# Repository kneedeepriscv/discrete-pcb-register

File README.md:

# discrete-pcb-register
PCB for the register for the KneeDeep RISCV Discrete Build

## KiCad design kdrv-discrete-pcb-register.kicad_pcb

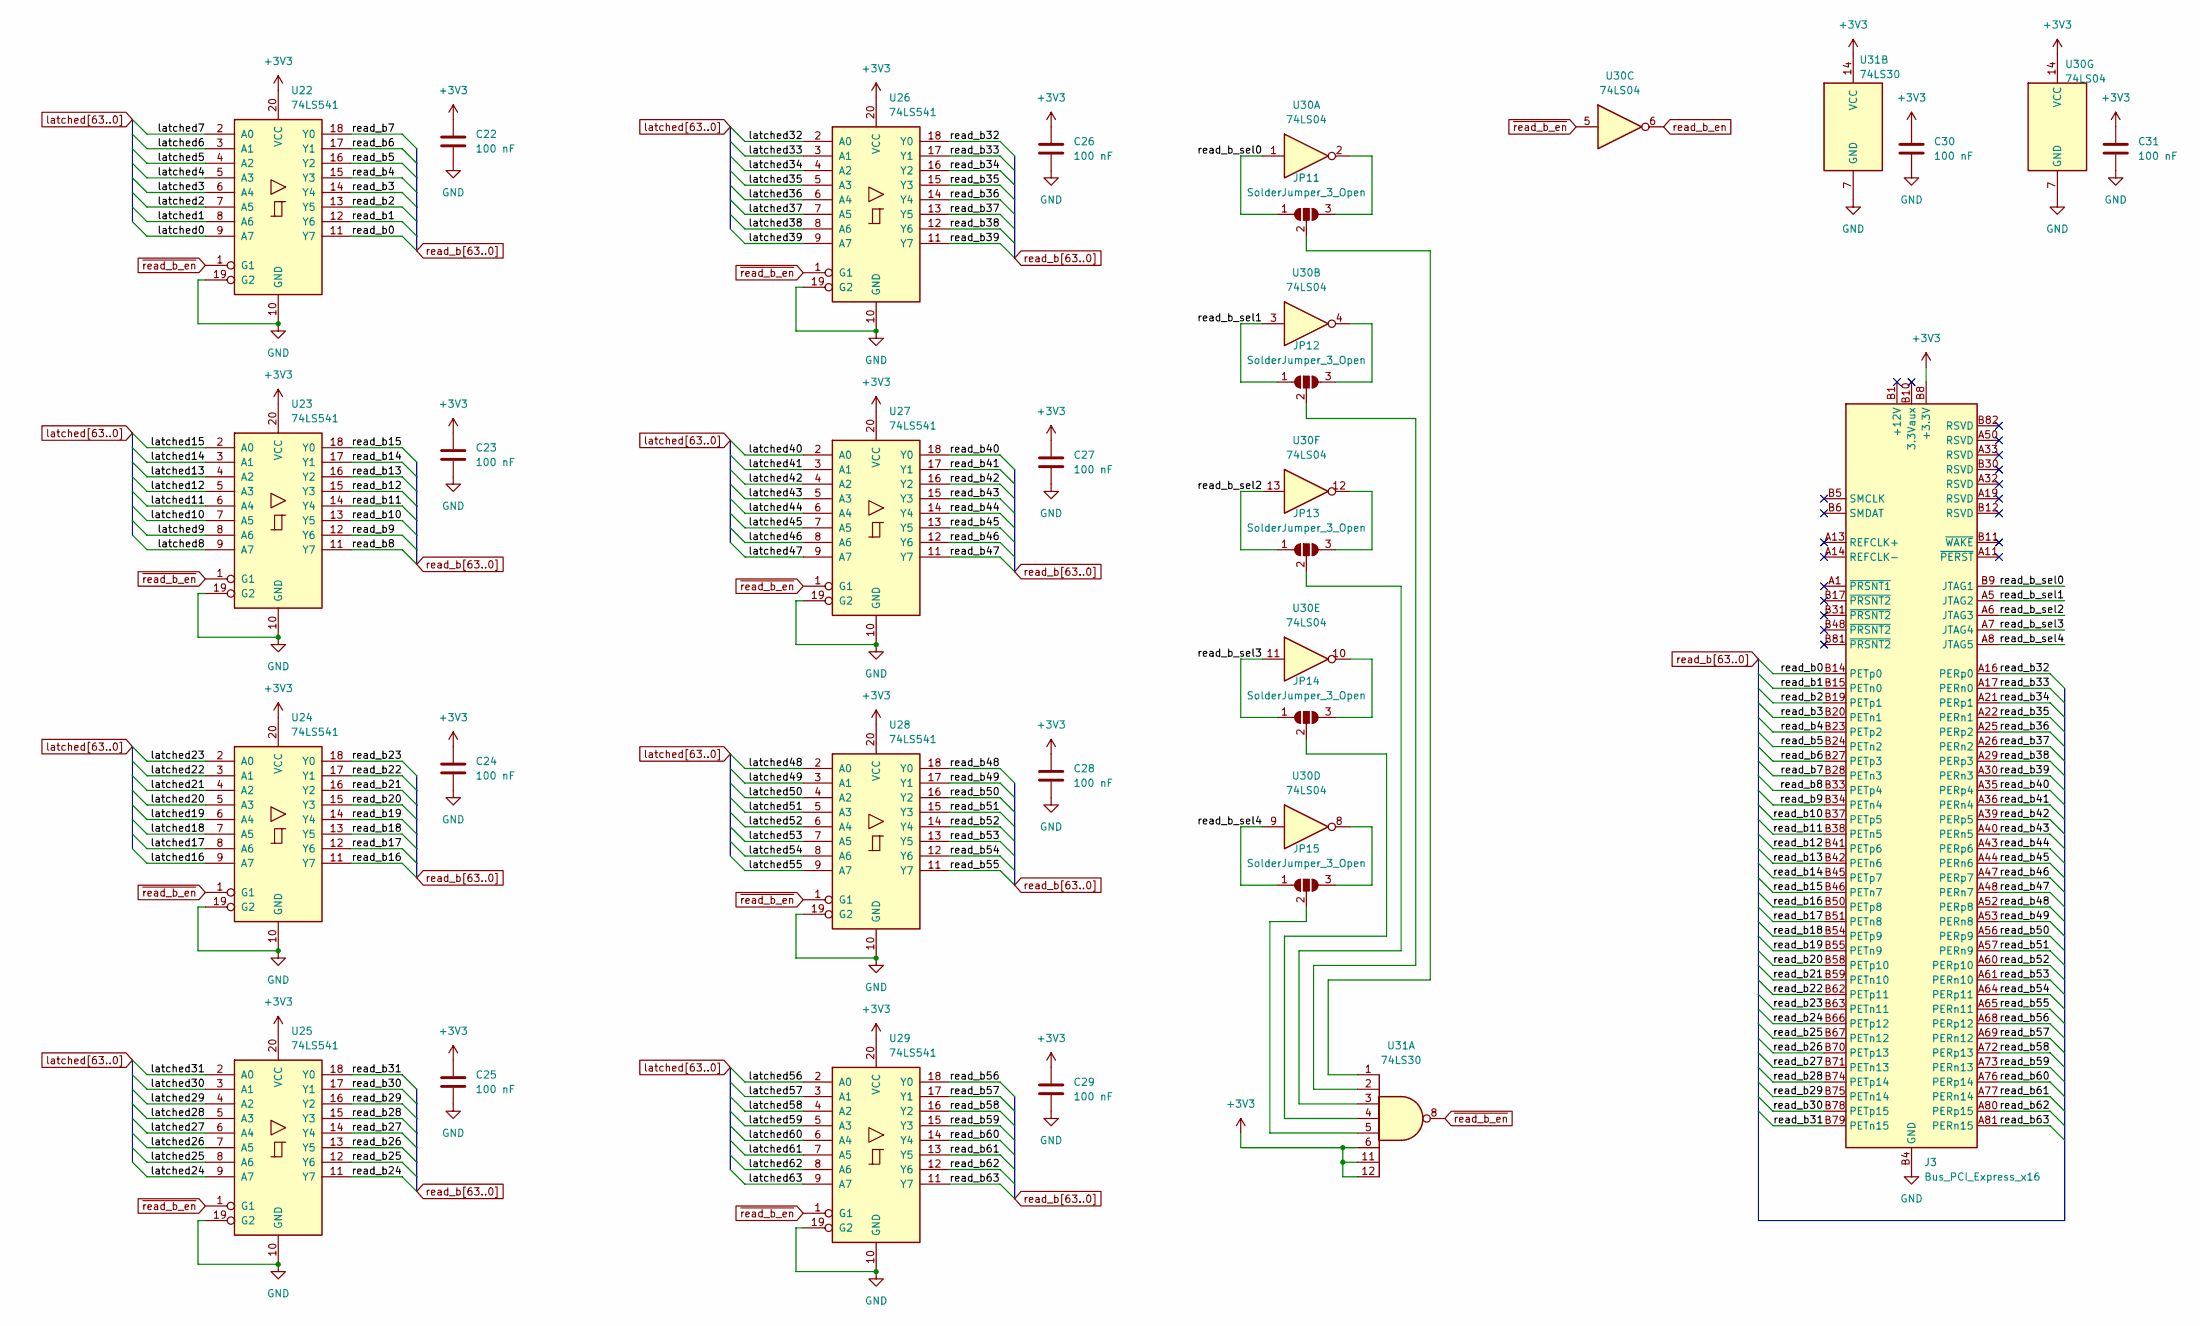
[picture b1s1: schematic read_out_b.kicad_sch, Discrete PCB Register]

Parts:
C22, C23, C24, C25, C26, C27, C28, C29, C30, C31: 100 nF; C_0805_2012Metric_Pad1.18x1.45mm_HandSolder
J3: Bus_PCI_Express_x16; BUS_PCIexpress_x16
JP11, JP12, JP13, JP14, JP15: SolderJumper_3_Open; SolderJumper-3_P1.3mm_Open_RoundedPad1.0x1.5mm
U22, U23, U24, U25, U26, U27, U28, U29: 74LS541; SOIC-20W_7.5x12.8mm_P1.27mm
U30: 74LS04; SOIC-14_3.9x8.7mm_P1.27mm
U31: 74LS30; SOIC-14_3.9x8.7mm_P1.27mm

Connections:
+3V3: C22.1, C23.1, C24.1, C25.1, C26.1, C27.1, C28.1, C29.1, C30.1, C31.1, J3.A9 (+3.3V), J3.A10 (+3.3V), J3.B8 (+3.3V), U22.20 (VCC), U23.20 (VCC), U24.20 (VCC), U25.20 (VCC), U26.20 (VCC), U27.20 (VCC), U28.20 (VCC), U29.20 (VCC), U30.14 (VCC), U31.6, U31.11, U31.12, U31.14 (VCC); also elsewhere on the board
/Read Out B/read_b_sel0: J3.B9 (JTAG1), JP11.1 (A), U30.1
/Read Out B/read_b_sel1: J3.A5 (JTAG2), JP12.1 (A), U30.3
/Read Out B/read_b_sel2: J3.A6 (JTAG3), JP13.1 (A), U30.13
/Read Out B/read_b_sel3: J3.A7 (JTAG4), JP14.1 (A), U30.11
/Read Out B/read_b_sel4: J3.A8 (JTAG5), JP15.1 (A), U30.9
GND: C22.2, C23.2, C24.2, C25.2, C26.2, C27.2, C28.2, C29.2, C30.2, C31.2, J3.A4 (GND), J3.A12 (GND), J3.A15 (GND), J3.A18 (GND), J3.A20 (GND), J3.A23 (GND), J3.A24 (GND), J3.A27 (GND), J3.A28 (GND), J3.A31 (GND), J3.A34 (GND), J3.A37 (GND), J3.A38 (GND), J3.A41 (GND), J3.A42 (GND), J3.A45 (GND), J3.A46 (GND), J3.A49 (GND), J3.A51 (GND), J3.A54 (GND), J3.A55 (GND), J3.A58 (GND), J3.A59 (GND), J3.A62 (GND), J3.A63 (GND), J3.A66 (GND), J3.A67 (GND), J3.A70 (GND), J3.A71 (GND), J3.A74 (GND), J3.A75 (GND), J3.A78 (GND), J3.A79 (GND), J3.A82 (GND), J3.B4 (GND), J3.B7 (GND), J3.B13 (GND), J3.B16 (GND), J3.B18 (GND), J3.B21 (GND), J3.B22 (GND), J3.B25 (GND), J3.B26 (GND), J3.B29 (GND), J3.B32 (GND), J3.B35 (GND), J3.B36 (GND), J3.B39 (GND), J3.B40 (GND), J3.B43 (GND), J3.B44 (GND), J3.B47 (GND), J3.B49 (GND), J3.B52 (GND), J3.B53 (GND), J3.B56 (GND), J3.B57 (GND), J3.B60 (GND), J3.B61 (GND), J3.B64 (GND), J3.B65 (GND), J3.B68 (GND), J3.B69 (GND), J3.B72 (GND), J3.B73 (GND), J3.B76 (GND), J3.B77 (GND), J3.B80 (GND), U22.10 (GND), U22.19 (G2), U23.10 (GND), U23.19 (G2), U24.10 (GND), U24.19 (G2), U25.10 (GND), U25.19 (G2), U26.10 (GND), U26.19 (G2), U27.10 (GND), U27.19 (G2), U28.10 (GND), U28.19 (G2), U29.10 (GND), U29.19 (G2), U30.7 (GND), U31.7 (GND); also elsewhere on the board
unnamed: JP11.3 (B), U30.2
unnamed: JP11.2 (C), U31.1
unnamed: JP12.3 (B), U30.4
unnamed: JP12.2 (C), U31.2
unnamed: JP13.3 (B), U30.12
unnamed: JP13.2 (C), U31.3
unnamed: JP14.3 (B), U30.10
unnamed: JP14.2 (C), U31.4
unnamed: JP15.3 (B), U30.8
unnamed: JP15.2 (C), U31.5
latched0: U22.9 (A7); also elsewhere on the board
latched1: U22.8 (A6); also elsewhere on the board
latched2: U22.7 (A5); also elsewhere on the board
latched3: U22.6 (A4); also elsewhere on the board
latched4: U22.5 (A3); also elsewhere on the board
latched5: U22.4 (A2); also elsewhere on the board
latched6: U22.3 (A1); also elsewhere on the board
latched7: U22.2 (A0); also elsewhere on the board
latched8: U23.9 (A7); also elsewhere on the board
latched9: U23.8 (A6); also elsewhere on the board
latched10: U23.7 (A5); also elsewhere on the board
latched11: U23.6 (A4); also elsewhere on the board
latched12: U23.5 (A3); also elsewhere on the board
latched13: U23.4 (A2); also elsewhere on the board
latched14: U23.3 (A1); also elsewhere on the board
latched15: U23.2 (A0); also elsewhere on the board
latched16: U24.9 (A7); also elsewhere on the board
latched17: U24.8 (A6); also elsewhere on the board
latched18: U24.7 (A5); also elsewhere on the board
latched19: U24.6 (A4); also elsewhere on the board
latched20: U24.5 (A3); also elsewhere on the board
latched21: U24.4 (A2); also elsewhere on the board
latched22: U24.3 (A1); also elsewhere on the board
latched23: U24.2 (A0); also elsewhere on the board
latched24: U25.9 (A7); also elsewhere on the board
latched25: U25.8 (A6); also elsewhere on the board
latched26: U25.7 (A5); also elsewhere on the board
latched27: U25.6 (A4); also elsewhere on the board
latched28: U25.5 (A3); also elsewhere on the board
latched29: U25.4 (A2); also elsewhere on the board
latched30: U25.3 (A1); also elsewhere on the board
latched31: U25.2 (A0); also elsewhere on the board
latched32: U26.2 (A0); also elsewhere on the board
latched33: U26.3 (A1); also elsewhere on the board
latched34: U26.4 (A2); also elsewhere on the board
latched35: U26.5 (A3); also elsewhere on the board
latched36: U26.6 (A4); also elsewhere on the board
latched37: U26.7 (A5); also elsewhere on the board
latched38: U26.8 (A6); also elsewhere on the board
latched39: U26.9 (A7); also elsewhere on the board
latched40: U27.2 (A0); also elsewhere on the board
latched41: U27.3 (A1); also elsewhere on the board
latched42: U27.4 (A2); also elsewhere on the board
latched43: U27.5 (A3); also elsewhere on the board
latched44: U27.6 (A4); also elsewhere on the board
latched45: U27.7 (A5); also elsewhere on the board
latched46: U27.8 (A6); also elsewhere on the board
latched47: U27.9 (A7); also elsewhere on the board
latched48: U28.2 (A0); also elsewhere on the board
latched49: U28.3 (A1); also elsewhere on the board
latched50: U28.4 (A2); also elsewhere on the board
latched51: U28.5 (A3); also elsewhere on the board
latched52: U28.6 (A4); also elsewhere on the board
latched53: U28.7 (A5); also elsewhere on the board
latched54: U28.8 (A6); also elsewhere on the board
latched55: U28.9 (A7); also elsewhere on the board
latched56: U29.2 (A0); also elsewhere on the board
latched57: U29.3 (A1); also elsewhere on the board
latched58: U29.4 (A2); also elsewhere on the board
latched59: U29.5 (A3); also elsewhere on the board
latched60: U29.6 (A4); also elsewhere on the board
latched61: U29.7 (A5); also elsewhere on the board
latched62: U29.8 (A6); also elsewhere on the board
latched63: U29.9 (A7); also elsewhere on the board
read_b0: J3.B14 (PETp0), U22.11 (Y7)
read_b1: J3.B15 (PETn0), U22.12 (Y6)
read_b2: J3.B19 (PETp1), U22.13 (Y5)
read_b3: J3.B20 (PETn1), U22.14 (Y4)
read_b4: J3.B23 (PETp2), U22.15 (Y3)
read_b5: J3.B24 (PETn2), U22.16 (Y2)
read_b6: J3.B27 (PETp3), U22.17 (Y1)
read_b7: J3.B28 (PETn3), U22.18 (Y0)
read_b8: J3.B33 (PETp4), U23.11 (Y7)
read_b9: J3.B34 (PETn4), U23.12 (Y6)
read_b10: J3.B37 (PETp5), U23.13 (Y5)
read_b11: J3.B38 (PETn5), U23.14 (Y4)
read_b12: J3.B41 (PETp6), U23.15 (Y3)
read_b13: J3.B42 (PETn6), U23.16 (Y2)
read_b14: J3.B45 (PETp7), U23.17 (Y1)
read_b15: J3.B46 (PETn7), U23.18 (Y0)
read_b16: J3.B50 (PETp8), U24.11 (Y7)
read_b17: J3.B51 (PETn8), U24.12 (Y6)
read_b18: J3.B54 (PETp9), U24.13 (Y5)
read_b19: J3.B55 (PETn9), U24.14 (Y4)
read_b20: J3.B58 (PETp10), U24.15 (Y3)
read_b21: J3.B59 (PETn10), U24.16 (Y2)
read_b22: J3.B62 (PETp11), U24.17 (Y1)
read_b23: J3.B63 (PETn11), U24.18 (Y0)
read_b24: J3.B66 (PETp12), U25.11 (Y7)
read_b25: J3.B67 (PETn12), U25.12 (Y6)
read_b26: J3.B70 (PETp13), U25.13 (Y5)
read_b27: J3.B71 (PETn13), U25.14 (Y4)
read_b28: J3.B74 (PETp14), U25.15 (Y3)
read_b29: J3.B75 (PETn14), U25.16 (Y2)
read_b30: J3.B78 (PETp15), U25.17 (Y1)
read_b31: J3.B79 (PETn15), U25.18 (Y0)
read_b32: J3.A16 (PERp0), U26.18 (Y0)
read_b33: J3.A17 (PERn0), U26.17 (Y1)
read_b34: J3.A21 (PERp1), U26.16 (Y2)
read_b35: J3.A22 (PERn1), U26.15 (Y3)
read_b36: J3.A25 (PERp2), U26.14 (Y4)
read_b37: J3.A26 (PERn2), U26.13 (Y5)
read_b38: J3.A29 (PERp3), U26.12 (Y6)
read_b39: J3.A30 (PERn3), U26.11 (Y7)
read_b40: J3.A35 (PERp4), U27.18 (Y0)
read_b41: J3.A36 (PERn4), U27.17 (Y1)
read_b42: J3.A39 (PERp5), U27.16 (Y2)
read_b43: J3.A40 (PERn5), U27.15 (Y3)
read_b44: J3.A43 (PERp6), U27.14 (Y4)
read_b45: J3.A44 (PERn6), U27.13 (Y5)
read_b46: J3.A47 (PERp7), U27.12 (Y6)
read_b47: J3.A48 (PERn7), U27.11 (Y7)
read_b48: J3.A52 (PERp8), U28.18 (Y0)
read_b49: J3.A53 (PERn8), U28.17 (Y1)
read_b50: J3.A56 (PERp9), U28.16 (Y2)
read_b51: J3.A57 (PERn9), U28.15 (Y3)
read_b52: J3.A60 (PERp10), U28.14 (Y4)
read_b53: J3.A61 (PERn10), U28.13 (Y5)
read_b54: J3.A64 (PERp11), U28.12 (Y6)
read_b55: J3.A65 (PERn11), U28.11 (Y7)
read_b56: J3.A68 (PERp12), U29.18 (Y0)
read_b57: J3.A69 (PERn12), U29.17 (Y1)
read_b58: J3.A72 (PERp13), U29.16 (Y2)
read_b59: J3.A73 (PERn13), U29.15 (Y3)
read_b60: J3.A76 (PERp14), U29.14 (Y4)
read_b61: J3.A77 (PERn14), U29.13 (Y5)
read_b62: J3.A80 (PERp15), U29.12 (Y6)
read_b63: J3.A81 (PERn15), U29.11 (Y7)
read_b_en: U30.6; also elsewhere on the board
~read_b_en: U22.1 (G1), U23.1 (G1), U24.1 (G1), U25.1 (G1), U26.1 (G1), U27.1 (G1), U28.1 (G1), U29.1 (G1), U30.5, U31.8

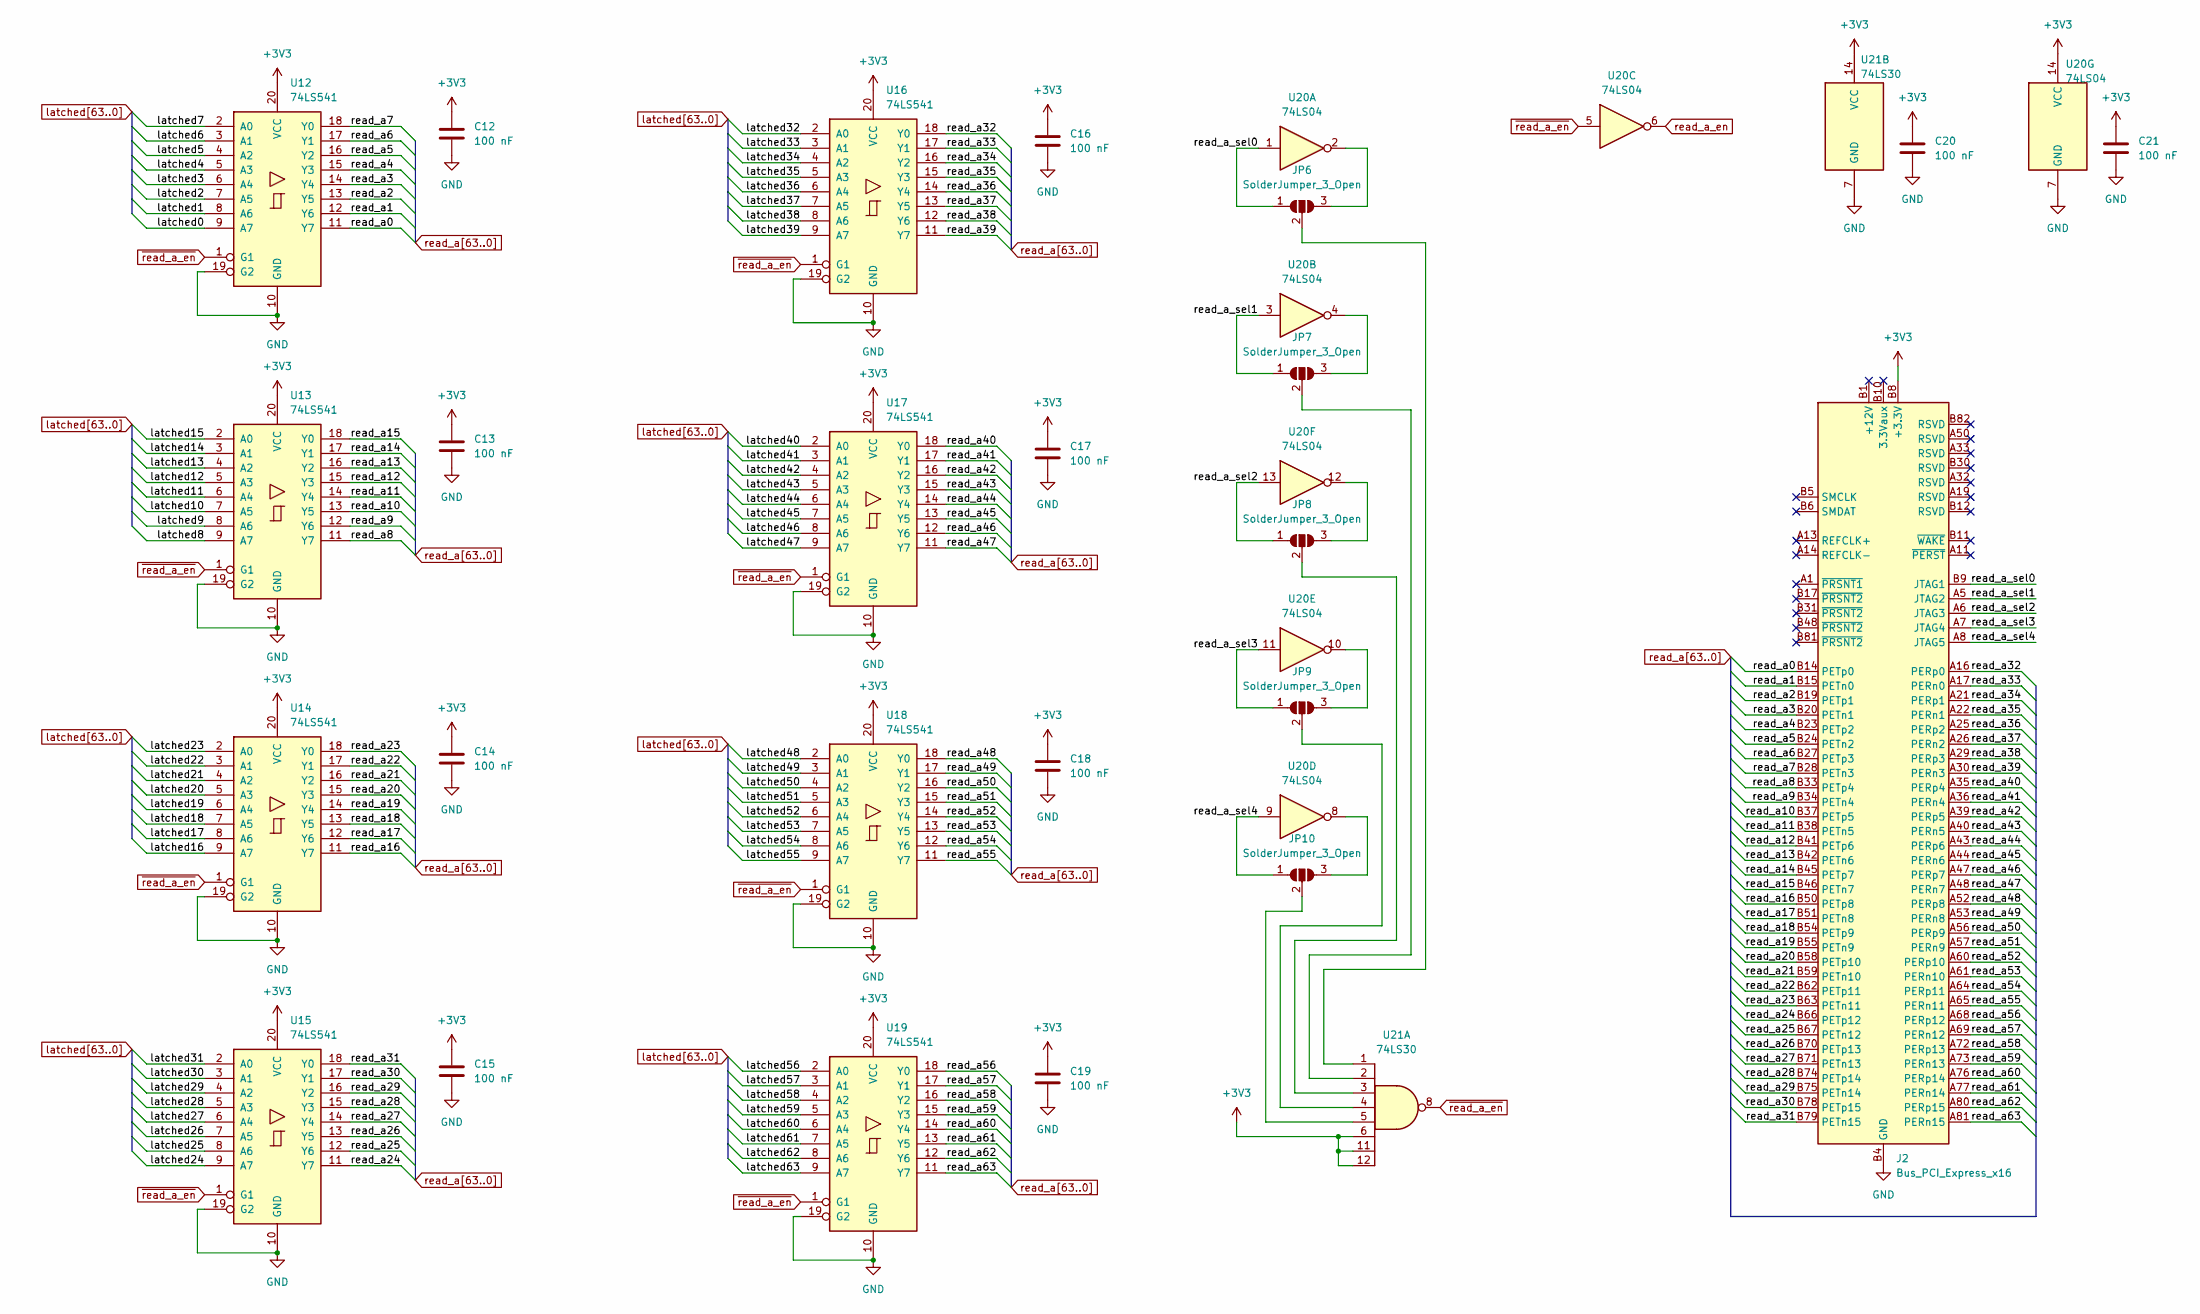
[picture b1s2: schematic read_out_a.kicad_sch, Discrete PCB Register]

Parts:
C12, C13, C14, C15, C16, C17, C18, C19, C20, C21: 100 nF; C_0805_2012Metric_Pad1.18x1.45mm_HandSolder
J2: Bus_PCI_Express_x16; BUS_PCIexpress_x16
JP6, JP7, JP8, JP9, JP10: SolderJumper_3_Open; SolderJumper-3_P1.3mm_Open_RoundedPad1.0x1.5mm
U12, U13, U14, U15, U16, U17, U18, U19: 74LS541; SOIC-20W_7.5x12.8mm_P1.27mm
U20: 74LS04; SOIC-14_3.9x8.7mm_P1.27mm
U21: 74LS30; SOIC-14_3.9x8.7mm_P1.27mm

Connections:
+3V3: C12.1, C13.1, C14.1, C15.1, C16.1, C17.1, C18.1, C19.1, C20.1, C21.1, J2.A9 (+3.3V), J2.A10 (+3.3V), J2.B8 (+3.3V), U12.20 (VCC), U13.20 (VCC), U14.20 (VCC), U15.20 (VCC), U16.20 (VCC), U17.20 (VCC), U18.20 (VCC), U19.20 (VCC), U20.14 (VCC), U21.6, U21.11, U21.12, U21.14 (VCC); also elsewhere on the board
/Read Out A/read_a_sel0: J2.B9 (JTAG1), JP6.1 (A), U20.1
/Read Out A/read_a_sel1: J2.A5 (JTAG2), JP7.1 (A), U20.3
/Read Out A/read_a_sel2: J2.A6 (JTAG3), JP8.1 (A), U20.13
/Read Out A/read_a_sel3: J2.A7 (JTAG4), JP9.1 (A), U20.11
/Read Out A/read_a_sel4: J2.A8 (JTAG5), JP10.1 (A), U20.9
GND: C12.2, C13.2, C14.2, C15.2, C16.2, C17.2, C18.2, C19.2, C20.2, C21.2, J2.A4 (GND), J2.A12 (GND), J2.A15 (GND), J2.A18 (GND), J2.A20 (GND), J2.A23 (GND), J2.A24 (GND), J2.A27 (GND), J2.A28 (GND), J2.A31 (GND), J2.A34 (GND), J2.A37 (GND), J2.A38 (GND), J2.A41 (GND), J2.A42 (GND), J2.A45 (GND), J2.A46 (GND), J2.A49 (GND), J2.A51 (GND), J2.A54 (GND), J2.A55 (GND), J2.A58 (GND), J2.A59 (GND), J2.A62 (GND), J2.A63 (GND), J2.A66 (GND), J2.A67 (GND), J2.A70 (GND), J2.A71 (GND), J2.A74 (GND), J2.A75 (GND), J2.A78 (GND), J2.A79 (GND), J2.A82 (GND), J2.B4 (GND), J2.B7 (GND), J2.B13 (GND), J2.B16 (GND), J2.B18 (GND), J2.B21 (GND), J2.B22 (GND), J2.B25 (GND), J2.B26 (GND), J2.B29 (GND), J2.B32 (GND), J2.B35 (GND), J2.B36 (GND), J2.B39 (GND), J2.B40 (GND), J2.B43 (GND), J2.B44 (GND), J2.B47 (GND), J2.B49 (GND), J2.B52 (GND), J2.B53 (GND), J2.B56 (GND), J2.B57 (GND), J2.B60 (GND), J2.B61 (GND), J2.B64 (GND), J2.B65 (GND), J2.B68 (GND), J2.B69 (GND), J2.B72 (GND), J2.B73 (GND), J2.B76 (GND), J2.B77 (GND), J2.B80 (GND), U12.10 (GND), U12.19 (G2), U13.10 (GND), U13.19 (G2), U14.10 (GND), U14.19 (G2), U15.10 (GND), U15.19 (G2), U16.10 (GND), U16.19 (G2), U17.10 (GND), U17.19 (G2), U18.10 (GND), U18.19 (G2), U19.10 (GND), U19.19 (G2), U20.7 (GND), U21.7 (GND); also elsewhere on the board
unnamed: JP6.3 (B), U20.2
unnamed: JP6.2 (C), U21.1
unnamed: JP7.3 (B), U20.4
unnamed: JP7.2 (C), U21.2
unnamed: JP8.3 (B), U20.12
unnamed: JP8.2 (C), U21.3
unnamed: JP9.3 (B), U20.10
unnamed: JP9.2 (C), U21.4
unnamed: JP10.3 (B), U20.8
unnamed: JP10.2 (C), U21.5
latched0: U12.9 (A7); also elsewhere on the board
latched1: U12.8 (A6); also elsewhere on the board
latched2: U12.7 (A5); also elsewhere on the board
latched3: U12.6 (A4); also elsewhere on the board
latched4: U12.5 (A3); also elsewhere on the board
latched5: U12.4 (A2); also elsewhere on the board
latched6: U12.3 (A1); also elsewhere on the board
latched7: U12.2 (A0); also elsewhere on the board
latched8: U13.9 (A7); also elsewhere on the board
latched9: U13.8 (A6); also elsewhere on the board
latched10: U13.7 (A5); also elsewhere on the board
latched11: U13.6 (A4); also elsewhere on the board
latched12: U13.5 (A3); also elsewhere on the board
latched13: U13.4 (A2); also elsewhere on the board
latched14: U13.3 (A1); also elsewhere on the board
latched15: U13.2 (A0); also elsewhere on the board
latched16: U14.9 (A7); also elsewhere on the board
latched17: U14.8 (A6); also elsewhere on the board
latched18: U14.7 (A5); also elsewhere on the board
latched19: U14.6 (A4); also elsewhere on the board
latched20: U14.5 (A3); also elsewhere on the board
latched21: U14.4 (A2); also elsewhere on the board
latched22: U14.3 (A1); also elsewhere on the board
latched23: U14.2 (A0); also elsewhere on the board
latched24: U15.9 (A7); also elsewhere on the board
latched25: U15.8 (A6); also elsewhere on the board
latched26: U15.7 (A5); also elsewhere on the board
latched27: U15.6 (A4); also elsewhere on the board
latched28: U15.5 (A3); also elsewhere on the board
latched29: U15.4 (A2); also elsewhere on the board
latched30: U15.3 (A1); also elsewhere on the board
latched31: U15.2 (A0); also elsewhere on the board
latched32: U16.2 (A0); also elsewhere on the board
latched33: U16.3 (A1); also elsewhere on the board
latched34: U16.4 (A2); also elsewhere on the board
latched35: U16.5 (A3); also elsewhere on the board
latched36: U16.6 (A4); also elsewhere on the board
latched37: U16.7 (A5); also elsewhere on the board
latched38: U16.8 (A6); also elsewhere on the board
latched39: U16.9 (A7); also elsewhere on the board
latched40: U17.2 (A0); also elsewhere on the board
latched41: U17.3 (A1); also elsewhere on the board
latched42: U17.4 (A2); also elsewhere on the board
latched43: U17.5 (A3); also elsewhere on the board
latched44: U17.6 (A4); also elsewhere on the board
latched45: U17.7 (A5); also elsewhere on the board
latched46: U17.8 (A6); also elsewhere on the board
latched47: U17.9 (A7); also elsewhere on the board
latched48: U18.2 (A0); also elsewhere on the board
latched49: U18.3 (A1); also elsewhere on the board
latched50: U18.4 (A2); also elsewhere on the board
latched51: U18.5 (A3); also elsewhere on the board
latched52: U18.6 (A4); also elsewhere on the board
latched53: U18.7 (A5); also elsewhere on the board
latched54: U18.8 (A6); also elsewhere on the board
latched55: U18.9 (A7); also elsewhere on the board
latched56: U19.2 (A0); also elsewhere on the board
latched57: U19.3 (A1); also elsewhere on the board
latched58: U19.4 (A2); also elsewhere on the board
latched59: U19.5 (A3); also elsewhere on the board
latched60: U19.6 (A4); also elsewhere on the board
latched61: U19.7 (A5); also elsewhere on the board
latched62: U19.8 (A6); also elsewhere on the board
latched63: U19.9 (A7); also elsewhere on the board
read_a0: J2.B14 (PETp0), U12.11 (Y7)
read_a1: J2.B15 (PETn0), U12.12 (Y6)
read_a2: J2.B19 (PETp1), U12.13 (Y5)
read_a3: J2.B20 (PETn1), U12.14 (Y4)
read_a4: J2.B23 (PETp2), U12.15 (Y3)
read_a5: J2.B24 (PETn2), U12.16 (Y2)
read_a6: J2.B27 (PETp3), U12.17 (Y1)
read_a7: J2.B28 (PETn3), U12.18 (Y0)
read_a8: J2.B33 (PETp4), U13.11 (Y7)
read_a9: J2.B34 (PETn4), U13.12 (Y6)
read_a10: J2.B37 (PETp5), U13.13 (Y5)
read_a11: J2.B38 (PETn5), U13.14 (Y4)
read_a12: J2.B41 (PETp6), U13.15 (Y3)
read_a13: J2.B42 (PETn6), U13.16 (Y2)
read_a14: J2.B45 (PETp7), U13.17 (Y1)
read_a15: J2.B46 (PETn7), U13.18 (Y0)
read_a16: J2.B50 (PETp8), U14.11 (Y7)
read_a17: J2.B51 (PETn8), U14.12 (Y6)
read_a18: J2.B54 (PETp9), U14.13 (Y5)
read_a19: J2.B55 (PETn9), U14.14 (Y4)
read_a20: J2.B58 (PETp10), U14.15 (Y3)
read_a21: J2.B59 (PETn10), U14.16 (Y2)
read_a22: J2.B62 (PETp11), U14.17 (Y1)
read_a23: J2.B63 (PETn11), U14.18 (Y0)
read_a24: J2.B66 (PETp12), U15.11 (Y7)
read_a25: J2.B67 (PETn12), U15.12 (Y6)
read_a26: J2.B70 (PETp13), U15.13 (Y5)
read_a27: J2.B71 (PETn13), U15.14 (Y4)
read_a28: J2.B74 (PETp14), U15.15 (Y3)
read_a29: J2.B75 (PETn14), U15.16 (Y2)
read_a30: J2.B78 (PETp15), U15.17 (Y1)
read_a31: J2.B79 (PETn15), U15.18 (Y0)
read_a32: J2.A16 (PERp0), U16.18 (Y0)
read_a33: J2.A17 (PERn0), U16.17 (Y1)
read_a34: J2.A21 (PERp1), U16.16 (Y2)
read_a35: J2.A22 (PERn1), U16.15 (Y3)
read_a36: J2.A25 (PERp2), U16.14 (Y4)
read_a37: J2.A26 (PERn2), U16.13 (Y5)
read_a38: J2.A29 (PERp3), U16.12 (Y6)
read_a39: J2.A30 (PERn3), U16.11 (Y7)
read_a40: J2.A35 (PERp4), U17.18 (Y0)
read_a41: J2.A36 (PERn4), U17.17 (Y1)
read_a42: J2.A39 (PERp5), U17.16 (Y2)
read_a43: J2.A40 (PERn5), U17.15 (Y3)
read_a44: J2.A43 (PERp6), U17.14 (Y4)
read_a45: J2.A44 (PERn6), U17.13 (Y5)
read_a46: J2.A47 (PERp7), U17.12 (Y6)
read_a47: J2.A48 (PERn7), U17.11 (Y7)
read_a48: J2.A52 (PERp8), U18.18 (Y0)
read_a49: J2.A53 (PERn8), U18.17 (Y1)
read_a50: J2.A56 (PERp9), U18.16 (Y2)
read_a51: J2.A57 (PERn9), U18.15 (Y3)
read_a52: J2.A60 (PERp10), U18.14 (Y4)
read_a53: J2.A61 (PERn10), U18.13 (Y5)
read_a54: J2.A64 (PERp11), U18.12 (Y6)
read_a55: J2.A65 (PERn11), U18.11 (Y7)
read_a56: J2.A68 (PERp12), U19.18 (Y0)
read_a57: J2.A69 (PERn12), U19.17 (Y1)
read_a58: J2.A72 (PERp13), U19.16 (Y2)
read_a59: J2.A73 (PERn13), U19.15 (Y3)
read_a60: J2.A76 (PERp14), U19.14 (Y4)
read_a61: J2.A77 (PERn14), U19.13 (Y5)
read_a62: J2.A80 (PERp15), U19.12 (Y6)
read_a63: J2.A81 (PERn15), U19.11 (Y7)
read_a_en: U20.6; also elsewhere on the board
~read_a_en: U12.1 (G1), U13.1 (G1), U14.1 (G1), U15.1 (G1), U16.1 (G1), U17.1 (G1), U18.1 (G1), U19.1 (G1), U20.5, U21.8

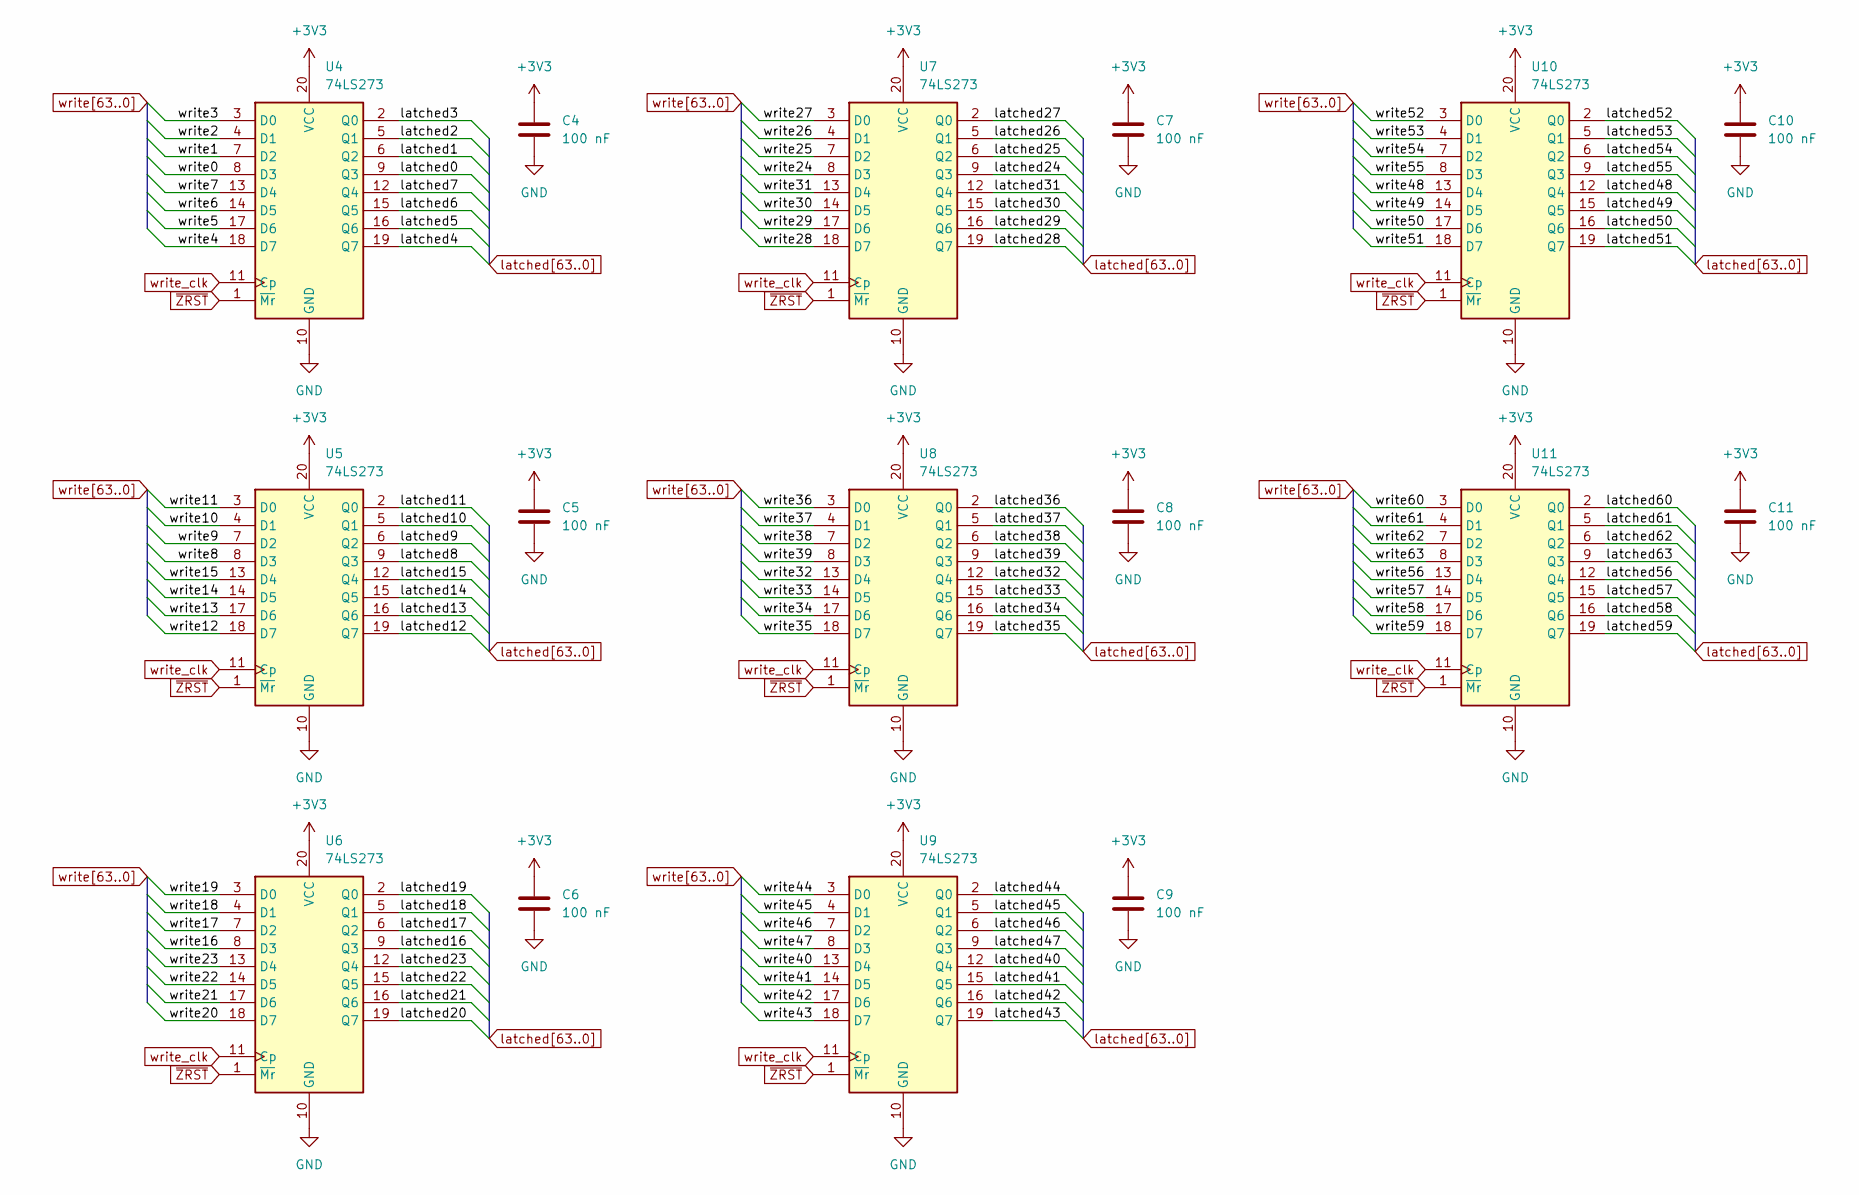
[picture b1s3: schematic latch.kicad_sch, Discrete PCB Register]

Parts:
C4, C5, C6, C7, C8, C9, C10, C11: 100 nF; C_0805_2012Metric_Pad1.18x1.45mm_HandSolder
U4, U5, U6, U7, U8, U9, U10, U11: 74LS273; SOIC-20W_7.5x12.8mm_P1.27mm

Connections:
+3V3: C4.1, C5.1, C6.1, C7.1, C8.1, C9.1, C10.1, C11.1, U4.20 (VCC), U5.20 (VCC), U6.20 (VCC), U7.20 (VCC), U8.20 (VCC), U9.20 (VCC), U10.20 (VCC), U11.20 (VCC); also elsewhere on the board
GND: C4.2, C5.2, C6.2, C7.2, C8.2, C9.2, C10.2, C11.2, U4.10 (GND), U5.10 (GND), U6.10 (GND), U7.10 (GND), U8.10 (GND), U9.10 (GND), U10.10 (GND), U11.10 (GND); also elsewhere on the board
latched0: U4.9 (Q3); also elsewhere on the board
latched1: U4.6 (Q2); also elsewhere on the board
latched2: U4.5 (Q1); also elsewhere on the board
latched3: U4.2 (Q0); also elsewhere on the board
latched4: U4.19 (Q7); also elsewhere on the board
latched5: U4.16 (Q6); also elsewhere on the board
latched6: U4.15 (Q5); also elsewhere on the board
latched7: U4.12 (Q4); also elsewhere on the board
latched8: U5.9 (Q3); also elsewhere on the board
latched9: U5.6 (Q2); also elsewhere on the board
latched10: U5.5 (Q1); also elsewhere on the board
latched11: U5.2 (Q0); also elsewhere on the board
latched12: U5.19 (Q7); also elsewhere on the board
latched13: U5.16 (Q6); also elsewhere on the board
latched14: U5.15 (Q5); also elsewhere on the board
latched15: U5.12 (Q4); also elsewhere on the board
latched16: U6.9 (Q3); also elsewhere on the board
latched17: U6.6 (Q2); also elsewhere on the board
latched18: U6.5 (Q1); also elsewhere on the board
latched19: U6.2 (Q0); also elsewhere on the board
latched20: U6.19 (Q7); also elsewhere on the board
latched21: U6.16 (Q6); also elsewhere on the board
latched22: U6.15 (Q5); also elsewhere on the board
latched23: U6.12 (Q4); also elsewhere on the board
latched24: U7.9 (Q3); also elsewhere on the board
latched25: U7.6 (Q2); also elsewhere on the board
latched26: U7.5 (Q1); also elsewhere on the board
latched27: U7.2 (Q0); also elsewhere on the board
latched28: U7.19 (Q7); also elsewhere on the board
latched29: U7.16 (Q6); also elsewhere on the board
latched30: U7.15 (Q5); also elsewhere on the board
latched31: U7.12 (Q4); also elsewhere on the board
latched32: U8.12 (Q4); also elsewhere on the board
latched33: U8.15 (Q5); also elsewhere on the board
latched34: U8.16 (Q6); also elsewhere on the board
latched35: U8.19 (Q7); also elsewhere on the board
latched36: U8.2 (Q0); also elsewhere on the board
latched37: U8.5 (Q1); also elsewhere on the board
latched38: U8.6 (Q2); also elsewhere on the board
latched39: U8.9 (Q3); also elsewhere on the board
latched40: U9.12 (Q4); also elsewhere on the board
latched41: U9.15 (Q5); also elsewhere on the board
latched42: U9.16 (Q6); also elsewhere on the board
latched43: U9.19 (Q7); also elsewhere on the board
latched44: U9.2 (Q0); also elsewhere on the board
latched45: U9.5 (Q1); also elsewhere on the board
latched46: U9.6 (Q2); also elsewhere on the board
latched47: U9.9 (Q3); also elsewhere on the board
latched48: U10.12 (Q4); also elsewhere on the board
latched49: U10.15 (Q5); also elsewhere on the board
latched50: U10.16 (Q6); also elsewhere on the board
latched51: U10.19 (Q7); also elsewhere on the board
latched52: U10.2 (Q0); also elsewhere on the board
latched53: U10.5 (Q1); also elsewhere on the board
latched54: U10.6 (Q2); also elsewhere on the board
latched55: U10.9 (Q3); also elsewhere on the board
latched56: U11.12 (Q4); also elsewhere on the board
latched57: U11.15 (Q5); also elsewhere on the board
latched58: U11.16 (Q6); also elsewhere on the board
latched59: U11.19 (Q7); also elsewhere on the board
latched60: U11.2 (Q0); also elsewhere on the board
latched61: U11.5 (Q1); also elsewhere on the board
latched62: U11.6 (Q2); also elsewhere on the board
latched63: U11.9 (Q3); also elsewhere on the board
write0: U4.8 (D3); also elsewhere on the board
write1: U4.7 (D2); also elsewhere on the board
write2: U4.4 (D1); also elsewhere on the board
write3: U4.3 (D0); also elsewhere on the board
write4: U4.18 (D7); also elsewhere on the board
write5: U4.17 (D6); also elsewhere on the board
write6: U4.14 (D5); also elsewhere on the board
write7: U4.13 (D4); also elsewhere on the board
write8: U5.8 (D3); also elsewhere on the board
write9: U5.7 (D2); also elsewhere on the board
write10: U5.4 (D1); also elsewhere on the board
write11: U5.3 (D0); also elsewhere on the board
write12: U5.18 (D7); also elsewhere on the board
write13: U5.17 (D6); also elsewhere on the board
write14: U5.14 (D5); also elsewhere on the board
write15: U5.13 (D4); also elsewhere on the board
write16: U6.8 (D3); also elsewhere on the board
write17: U6.7 (D2); also elsewhere on the board
write18: U6.4 (D1); also elsewhere on the board
write19: U6.3 (D0); also elsewhere on the board
write20: U6.18 (D7); also elsewhere on the board
write21: U6.17 (D6); also elsewhere on the board
write22: U6.14 (D5); also elsewhere on the board
write23: U6.13 (D4); also elsewhere on the board
write24: U7.8 (D3); also elsewhere on the board
write25: U7.7 (D2); also elsewhere on the board
write26: U7.4 (D1); also elsewhere on the board
write27: U7.3 (D0); also elsewhere on the board
write28: U7.18 (D7); also elsewhere on the board
write29: U7.17 (D6); also elsewhere on the board
write30: U7.14 (D5); also elsewhere on the board
write31: U7.13 (D4); also elsewhere on the board
write32: U8.13 (D4); also elsewhere on the board
write33: U8.14 (D5); also elsewhere on the board
write34: U8.17 (D6); also elsewhere on the board
write35: U8.18 (D7); also elsewhere on the board
write36: U8.3 (D0); also elsewhere on the board
write37: U8.4 (D1); also elsewhere on the board
write38: U8.7 (D2); also elsewhere on the board
write39: U8.8 (D3); also elsewhere on the board
write40: U9.13 (D4); also elsewhere on the board
write41: U9.14 (D5); also elsewhere on the board
write42: U9.17 (D6); also elsewhere on the board
write43: U9.18 (D7); also elsewhere on the board
write44: U9.3 (D0); also elsewhere on the board
write45: U9.4 (D1); also elsewhere on the board
write46: U9.7 (D2); also elsewhere on the board
write47: U9.8 (D3); also elsewhere on the board
write48: U10.13 (D4); also elsewhere on the board
write49: U10.14 (D5); also elsewhere on the board
write50: U10.17 (D6); also elsewhere on the board
write51: U10.18 (D7); also elsewhere on the board
write52: U10.3 (D0); also elsewhere on the board
write53: U10.4 (D1); also elsewhere on the board
write54: U10.7 (D2); also elsewhere on the board
write55: U10.8 (D3); also elsewhere on the board
write56: U11.13 (D4); also elsewhere on the board
write57: U11.14 (D5); also elsewhere on the board
write58: U11.17 (D6); also elsewhere on the board
write59: U11.18 (D7); also elsewhere on the board
write60: U11.3 (D0); also elsewhere on the board
write61: U11.4 (D1); also elsewhere on the board
write62: U11.7 (D2); also elsewhere on the board
write63: U11.8 (D3); also elsewhere on the board
write_clk: U4.11 (Cp), U5.11 (Cp), U6.11 (Cp), U7.11 (Cp), U8.11 (Cp), U9.11 (Cp), U10.11 (Cp), U11.11 (Cp); also elsewhere on the board
~ZRST: U4.1 (~Mr), U5.1 (~Mr), U6.1 (~Mr), U7.1 (~Mr), U8.1 (~Mr), U9.1 (~Mr), U10.1 (~Mr), U11.1 (~Mr); also elsewhere on the board
